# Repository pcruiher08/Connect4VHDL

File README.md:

Connect4VHDL is a repo that holds all the codes and designs for my Advandced Digital Systems Laboratory Final Project.

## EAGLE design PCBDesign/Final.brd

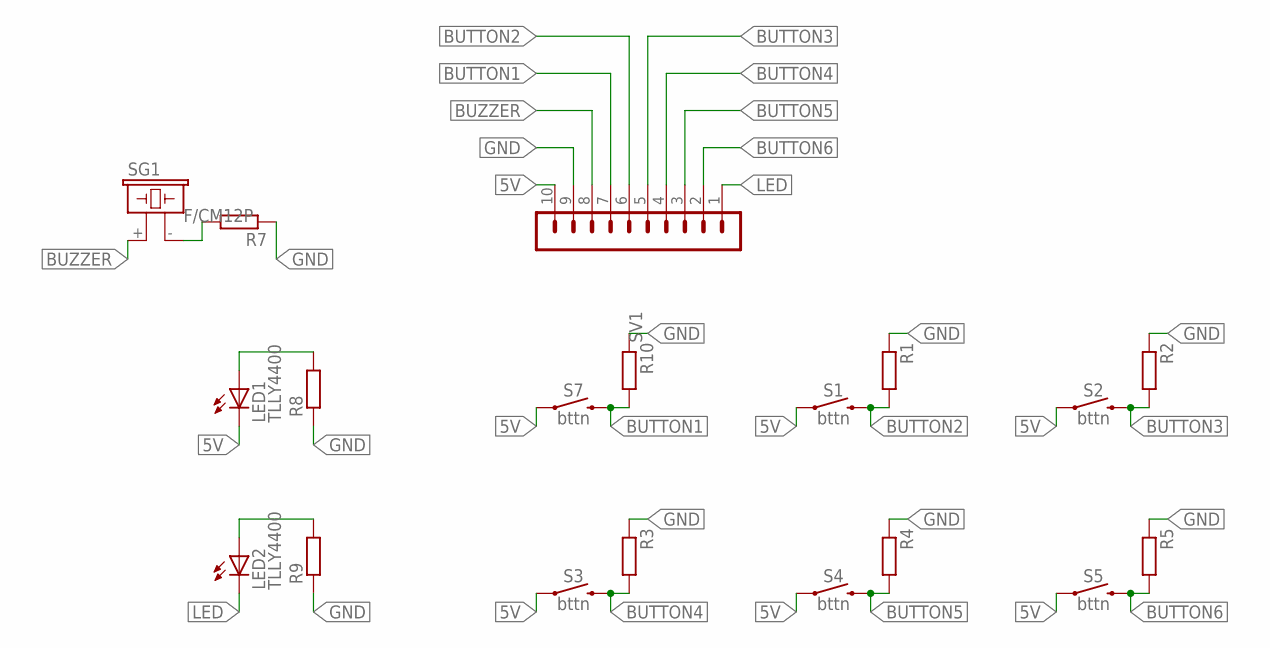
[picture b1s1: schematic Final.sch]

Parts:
LED1, LED2: TLLY4400; LED3MM
R1, R2, R3, R4, R5, R7, R8, R9, R10: R0204/7; 0204/7
S1, S2, S3, S4, S5, S7: bttn; TACTILE_SWITCH_PTH_6.0MM
SG1: F/CM12P
SV1: MA10-1

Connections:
5V: LED1.K (C), S1.1, S2.1, S3.1, S4.1, S5.1, S7.1, SV1.10
BUTTON1: R10.2, S7.3 (2), SV1.7
BUTTON2: R1.2, S1.3 (2), SV1.6
BUTTON3: R2.2, S2.3 (2), SV1.5
BUTTON4: R3.2, S3.3 (2), SV1.4
BUTTON5: R4.2, S4.3 (2), SV1.3
BUTTON6: R5.2, S5.3 (2), SV1.2
BUZZER: SG1.+ (1), SV1.8
GND: R1.1, R2.1, R3.1, R4.1, R5.1, R7.1, R8.1, R9.1, R10.1, SV1.9
LED: LED2.K (C), SV1.1
unnamed: R7.2, SG1.- (2)
unnamed: LED2.A, R9.2
unnamed: LED1.A, R8.2

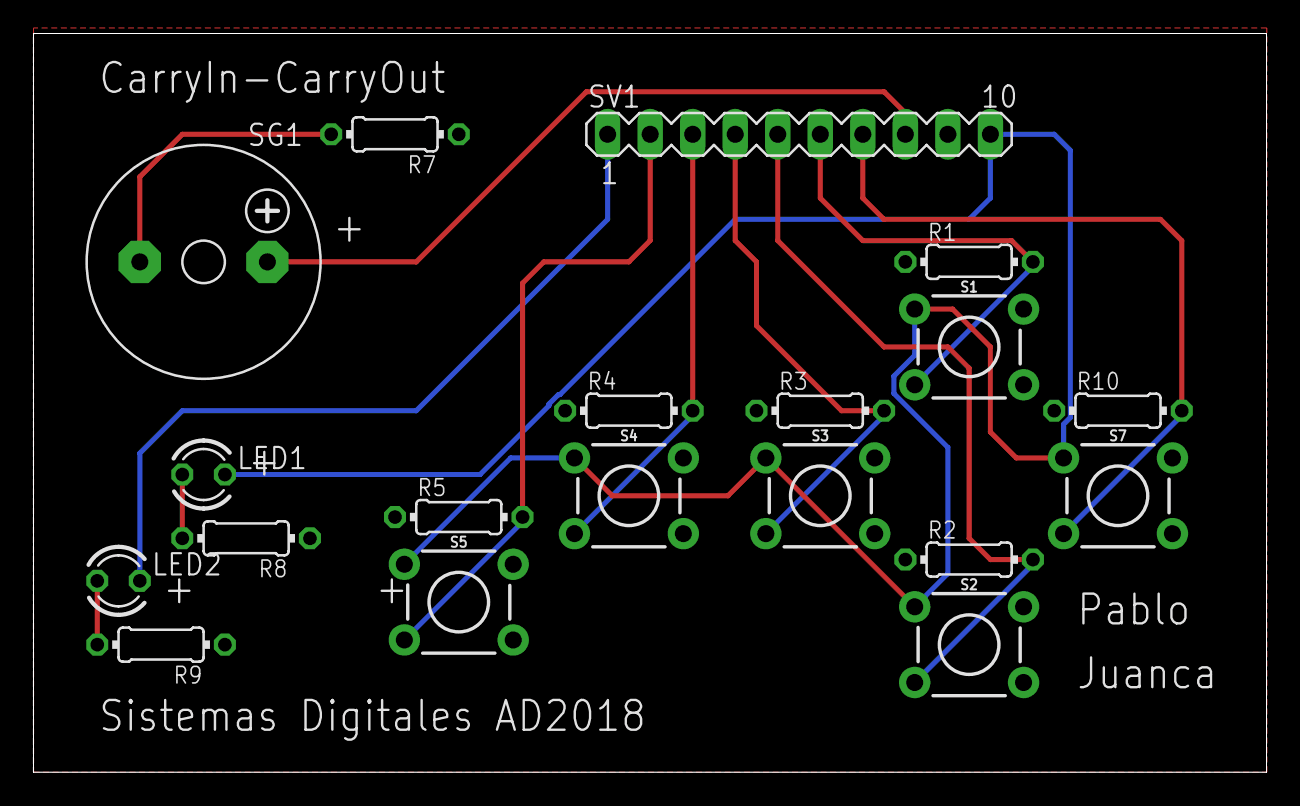
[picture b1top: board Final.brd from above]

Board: 2 copper layers, 73.6 x 44.1 mm, 19 parts (0 on the bottom side), 13 nets.

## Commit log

2018-12-02 added VHDL code for the vga controller
2018-12-02 generated the ucf file for spartan 3 debugging
2018-12-02 added eagle desigpcb designs
2018-12-02 Create README.md
    Added readme
2018-12-02 corrected board boundaries
2018-12-02 added all the board lines
2018-12-02 corrected some identation
2018-12-02 changed board colors
2018-12-02 added more clocks and vectors for columns and rows
2018-12-02 fixed clock
2018-12-02 added another component
2018-12-02 commited changes
2018-12-02 identations
2018-12-02 added selector
2018-12-02 corrected the selector, now working with left and right buttons on spartan 3
2018-12-02 working white selector
2018-12-03 working version saving the actual column and indicator led on blue board
2018-12-03 added some features
2018-12-03 added piece drop
2018-12-03 fixed first drop
2018-12-03 validations
2018-12-03 added lower limits
2018-12-03 full board
2018-12-03 empty board
2018-12-03 added no trimmed signals
2018-12-04 added code
2018-12-04 more
2018-12-04 more things
2018-12-04 more things added
2018-12-04 corrected columns
2018-12-04 case test
2018-12-04 another test
2018-12-04 removing t
2018-12-04 reset test
2018-12-04 reset test failed
2018-12-04 tie test
2018-12-04 tie test 2
2018-12-04 tie and win test
2018-12-04 tie and win test red
2018-12-04 tie and win test red and yellow
2018-12-04 tie and win test red and yellow with new process
2018-12-04 restart attemt with win or tie
2018-12-04 missing restart, everything else done
2018-12-04 win validation but no reset
2018-12-04 DONE

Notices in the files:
parts and their libraries:
SparkFun-Switches: Licensing: Creative Commons ShareAlike 4.0 International - https://creativecommons.org/licenses/by-sa/4.0
